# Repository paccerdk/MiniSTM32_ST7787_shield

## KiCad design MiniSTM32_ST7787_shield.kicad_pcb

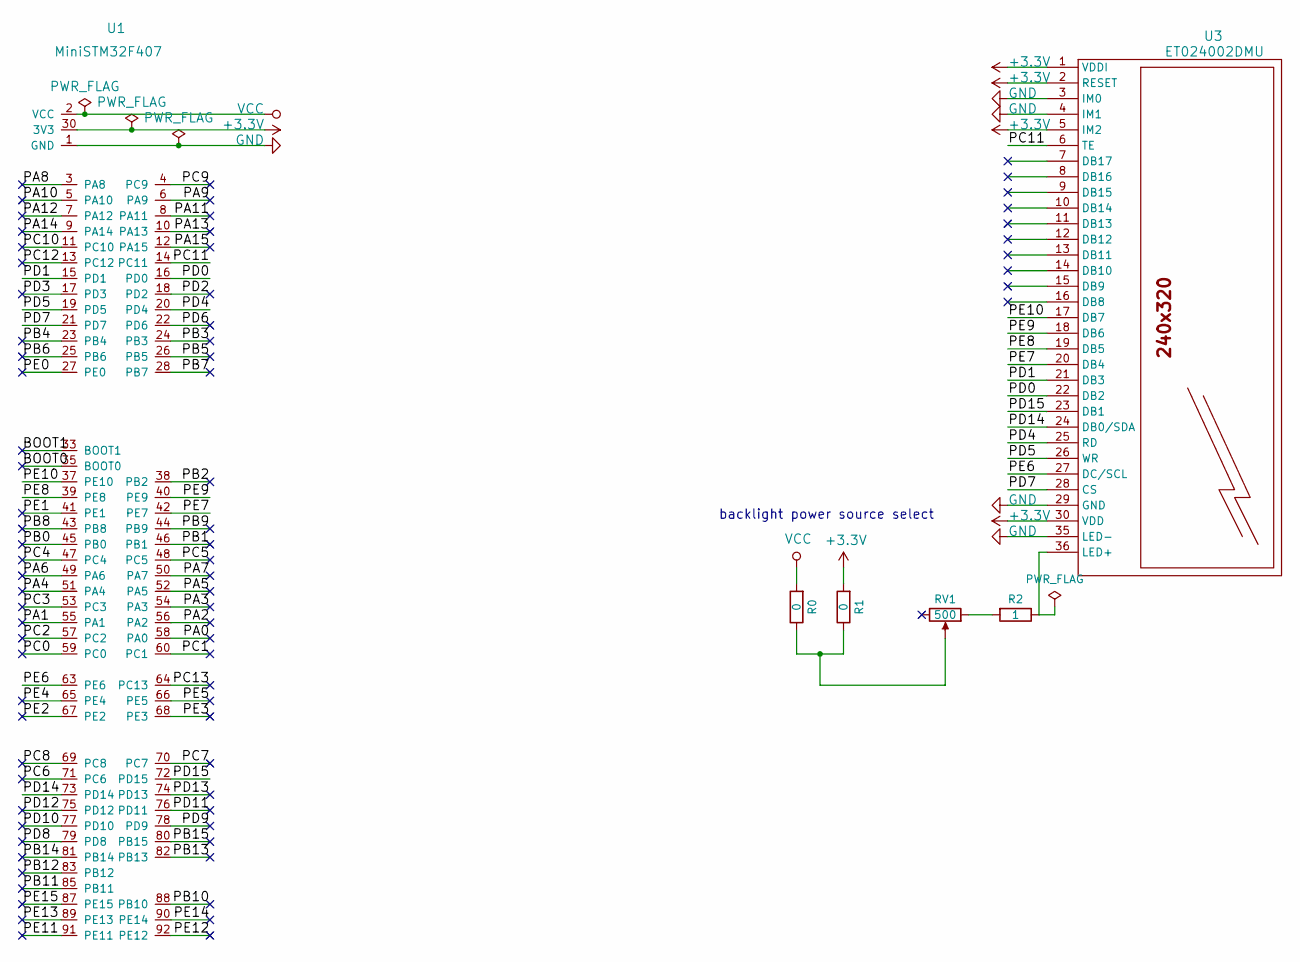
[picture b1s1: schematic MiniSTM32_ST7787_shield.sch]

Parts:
R0, R1: 0; R_0805_HandSoldering
R2: 1; R_0805_HandSoldering
RV1: 500; Potentiometer_Trimmer_Bourns_3296W
U1: MiniSTM32F407; MiniSTM32F407_PinsRemoved
U3: ET024002DMU; ET024002DMUrev2

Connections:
+3V3: R1.2, U1.30 (3V3), U1.61 (3V3), U1.84 (3V3), U3.1 (VDDI), U3.2 (RESET), U3.5 (IM2), U3.30 (VDD)
/BOOT0: U1.35 (BOOT0)
/BOOT1: U1.33 (BOOT1)
/PA0: U1.58 (PA0)
/PA1: U1.55 (PA1)
/PA2: U1.56 (PA2)
/PA3: U1.54 (PA3)
/PA4: U1.51 (PA4)
/PA5: U1.52 (PA5)
/PA6: U1.49 (PA6)
/PA7: U1.50 (PA7)
/PA8: U1.3 (PA8)
/PA9: U1.6 (PA9)
/PA10: U1.5 (PA10)
/PA11: U1.8 (PA11)
/PA12: U1.7 (PA12)
/PA13: U1.10 (PA13)
/PA14: U1.9 (PA14)
/PA15: U1.12 (PA15)
/PB0: U1.45 (PB0)
/PB1: U1.46 (PB1)
/PB2: U1.38 (PB2)
/PB3: U1.24 (PB3)
/PB4: U1.23 (PB4)
/PB5: U1.26 (PB5)
/PB6: U1.25 (PB6)
/PB7: U1.28 (PB7)
/PB8: U1.43 (PB8)
/PB9: U1.44 (PB9)
/PB10: U1.88 (PB10)
/PB11: U1.85 (PB11)
/PB12: U1.83 (PB12)
/PB13: U1.82 (PB13)
/PB14: U1.81 (PB14)
/PB15: U1.80 (PB15)
/PC0: U1.59 (PC0)
/PC1: U1.60 (PC1)
/PC2: U1.57 (PC2)
/PC3: U1.53 (PC3)
/PC4: U1.47 (PC4)
/PC5: U1.48 (PC5)
/PC6: U1.71 (PC6)
/PC7: U1.70 (PC7)
/PC8: U1.69 (PC8)
/PC9: U1.4 (PC9)
/PC10: U1.11 (PC10)
/PC11: U1.14 (PC11), U3.6 (TE)
/PC12: U1.13 (PC12)
/PC13: U1.64 (PC13)
/PD0: U1.16 (PD0), U3.22 (DB2)
/PD1: U1.15 (PD1), U3.21 (DB3)
/PD2: U1.18 (PD2)
/PD3: U1.17 (PD3)
/PD4: U1.20 (PD4), U3.25 (RD)
/PD5: U1.19 (PD5), U3.26 (WR)
/PD6: U1.22 (PD6)
/PD7: U1.21 (PD7), U3.28 (CS)
/PD8: U1.79 (PD8)
/PD9: U1.78 (PD9)
/PD10: U1.77 (PD10)
/PD11: U1.76 (PD11)
/PD12: U1.75 (PD12)
/PD13: U1.74 (PD13)
/PD14: U1.73 (PD14), U3.24 (DB0/SDA)
/PD15: U1.72 (PD15), U3.23 (DB1)
/PE0: U1.27 (PE0)
/PE1: U1.41 (PE1)
/PE2: U1.67 (PE2)
/PE3: U1.68 (PE3)
/PE4: U1.65 (PE4)
/PE5: U1.66 (PE5)
/PE6: U1.63 (PE6), U3.27 (DC/SCL)
/PE7: U1.42 (PE7), U3.20 (DB4)
/PE8: U1.39 (PE8), U3.19 (DB5)
/PE9: U1.40 (PE9), U3.18 (DB6)
/PE10: U1.37 (PE10), U3.17 (DB7)
/PE11: U1.91 (PE11)
/PE12: U1.92 (PE12)
/PE13: U1.89 (PE13)
/PE14: U1.90 (PE14)
/PE15: U1.87 (PE15)
GND: U1.1 (GND), U1.29 (GND), U1.31 (GND), U1.34 (GND), U1.36 (GND), U1.62 (GND), U1.86 (GND), U3.3 (IM0), U3.4 (IM1), U3.29 (GND), U3.35 (LED-)
unnamed: R0.1, R1.1, RV1.2
unnamed: R2.1, U3.36 (LED+)
unnamed: R2.2, RV1.1
VCC: R0.2, U1.2 (VCC), U1.32 (VCC)

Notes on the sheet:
backlight power source select

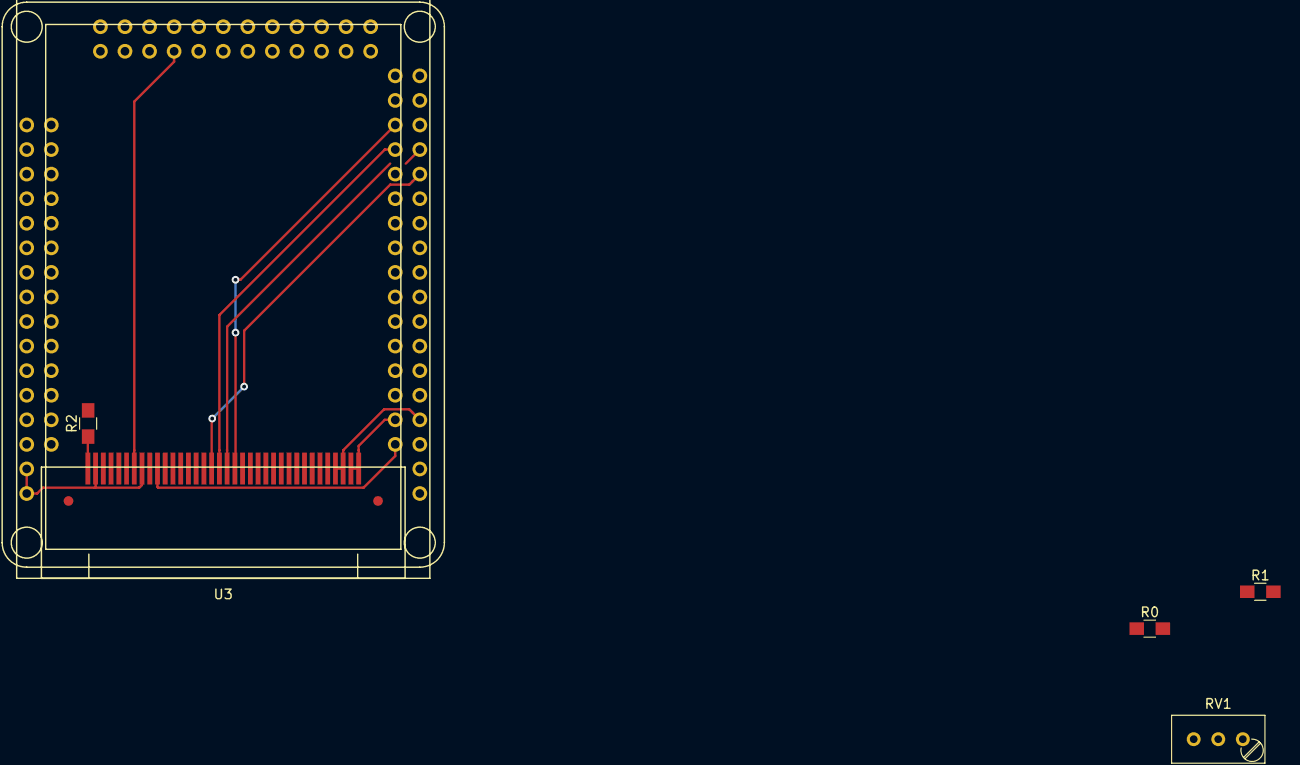
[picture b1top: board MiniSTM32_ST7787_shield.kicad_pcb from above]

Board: 2 copper layers, 6 parts (0 on the bottom side), 19 nets.

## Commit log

2017-11-01 schematic
2017-11-05 WIP
    work in progress
